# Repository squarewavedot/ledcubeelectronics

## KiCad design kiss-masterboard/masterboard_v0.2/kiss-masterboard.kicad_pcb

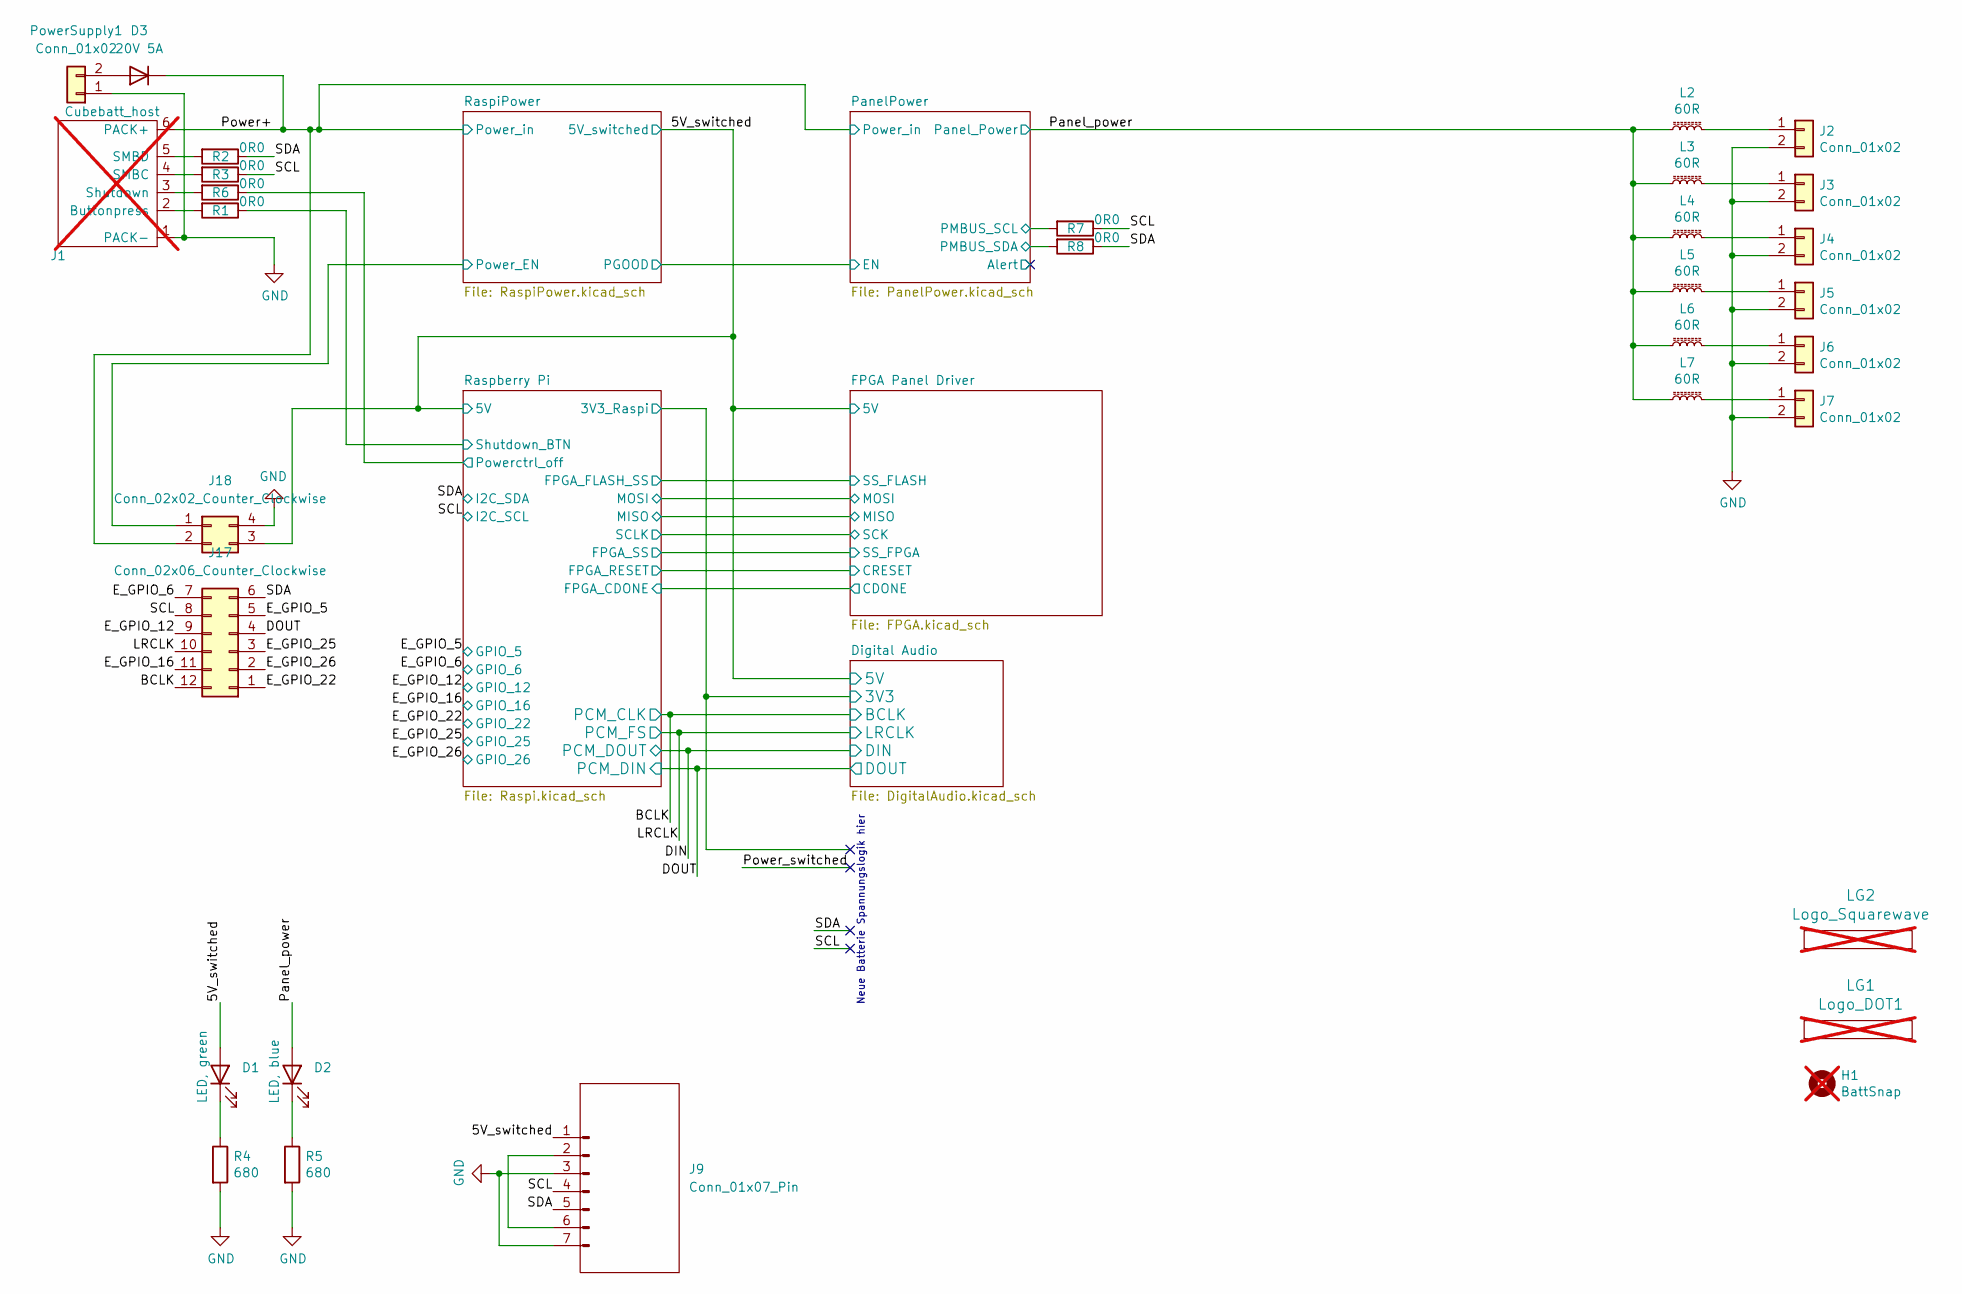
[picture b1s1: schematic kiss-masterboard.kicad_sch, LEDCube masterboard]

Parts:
D1: LED, green; LED_0603_1608Metric; Part No. LG Q971-KN-1; LCSC Part # C2290
D2: LED, blue; LED_0603_1608Metric; Part No. LB Q39G-L2N2-35-1; LCSC Part # C2286
D3: 20V 5A; D_SMA; LCSC Part # C5818966
H1: BattSnap; batt_snap; not fitted
J1: Cubebatt_host; cubebatt_host; not fitted
J2, J3, J4, J5, J6, J7: Conn_01x02; JST_VH_B2P-VH_1x02_P3.96mm_Vertical
J9: Conn_01x07_Pin; PinHeader_1x07_imu
J17: Conn_02x06_Counter_Clockwise; PinSocket_2x06_P2.54mm_Vertical_SMD; LCSC Part # C32713286
J18: Conn_02x02_Counter_Clockwise; PinSocket_2x02_P2.54mm_Vertical_SMD; LCSC Part # C919361
L2, L3, L4, L5, L6, L7: 60R; L_1008_2520Metric; Part No. FBMJ3216HM600-T; Digikey No. 587-1770-1-ND
LG1: Logo_DOT1; Logo_Dot_15mm_Text_Mask; not fitted
LG2: Logo_Squarewave; Logo_Squarewave_Text_15mm_Silks; not fitted
PowerSupply1: Conn_01x02; AMASS_XT30PW-F_1x02_P2.50mm_Horizontal
R1, R2, R3, R6, R7, R8: 0R0; R_0603_1608Metric; Part No. RC0603JR-07680R; LCSC Part # C21189
R4, R5: 680; R_0603_1608Metric; Part No. RC0603JR-07680R; LCSC Part # C23228

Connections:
/5V_switched: D1.2 (A), J9.1, J18.3; also elsewhere on the board
/BCLK: J17.12; also elsewhere on the board
/DOUT: J17.4; also elsewhere on the board
/E_GPIO_5: J17.5; also elsewhere on the board
/E_GPIO_6: J17.7; also elsewhere on the board
/E_GPIO_12: J17.9; also elsewhere on the board
/E_GPIO_16: J17.11; also elsewhere on the board
/E_GPIO_22: J17.1; also elsewhere on the board
/E_GPIO_25: J17.3; also elsewhere on the board
/E_GPIO_26: J17.2; also elsewhere on the board
/LRCLK: J17.10; also elsewhere on the board
/PanelPower/PMBUS_SCL: R7.2; also elsewhere on the board
/PanelPower/PMBUS_SDA: R8.2; also elsewhere on the board
/Panel_power: D2.2 (A), L2.1, L3.1, L4.1, L5.1, L6.1, L7.1; also elsewhere on the board
/Power+: D3.1 (K), J1.6 (PACK+), J18.2; also elsewhere on the board
/Raspberry Pi/Powerctrl_off: R6.1; also elsewhere on the board
/Raspberry Pi/Shutdown_BTN: R1.1; also elsewhere on the board
/RaspiPower/Power_EN: J18.1; also elsewhere on the board
/SCL: J9.4, J17.8, R3.1, R7.1; also elsewhere on the board
/SDA: J9.5, J17.6, R2.1, R8.1; also elsewhere on the board
GND: J1.1 (PACK-), J2.2, J3.2, J4.2, J5.2, J6.2, J7.2, J9.3, J9.7, J18.4, PowerSupply1.1, R4.2, R5.2; also elsewhere on the board
unnamed: D1.1 (K), R4.1
unnamed: D2.1 (K), R5.1
unnamed: D3.2 (A), PowerSupply1.2
unnamed: J1.2 (Buttonpress), R1.2
unnamed: J1.4 (SMBC), R3.2
unnamed: J1.5 (SMBD), R2.2
unnamed: J1.3 (Shutdown), R6.2
unnamed: J2.1, L2.2
unnamed: J3.1, L3.2
unnamed: J4.1, L4.2
unnamed: J5.1, L5.2
unnamed: J6.1, L6.2
unnamed: J7.1, L7.2
unnamed: J9.2, J9.6

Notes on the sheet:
Neue Batterie Spannungslogik hier

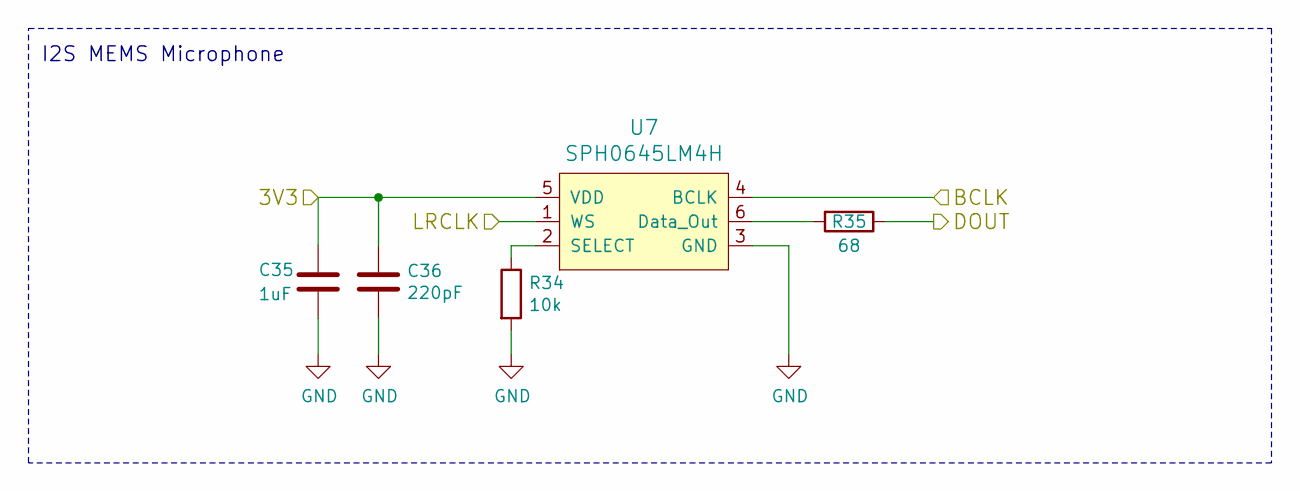
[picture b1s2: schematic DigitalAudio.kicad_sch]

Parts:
C35: 1uF; C_0603_1608Metric; LCSC Part # C15849
C36: 220pF; C_0603_1608Metric; LCSC Part # C1603
R34: 10k; R_0603_1608Metric; LCSC Part # C25804
R35: 68; R_0603_1608Metric; LCSC Part # C27592
U7: SPH0645LM4H

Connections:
/BCLK: U7.4 (BCLK); also elsewhere on the board
/DOUT: R35.1; also elsewhere on the board
/LRCLK: U7.1 (WS); also elsewhere on the board
/Raspberry Pi/3v3: C35.1, C36.1, U7.5 (VDD); also elsewhere on the board
GND: C35.2, C36.2, R34.2, U7.3 (GND); also elsewhere on the board
unnamed: R35.2, U7.6 (Data_Out)
unnamed: R34.1, U7.2 (SELECT)

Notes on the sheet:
I2S MEMS Microphone

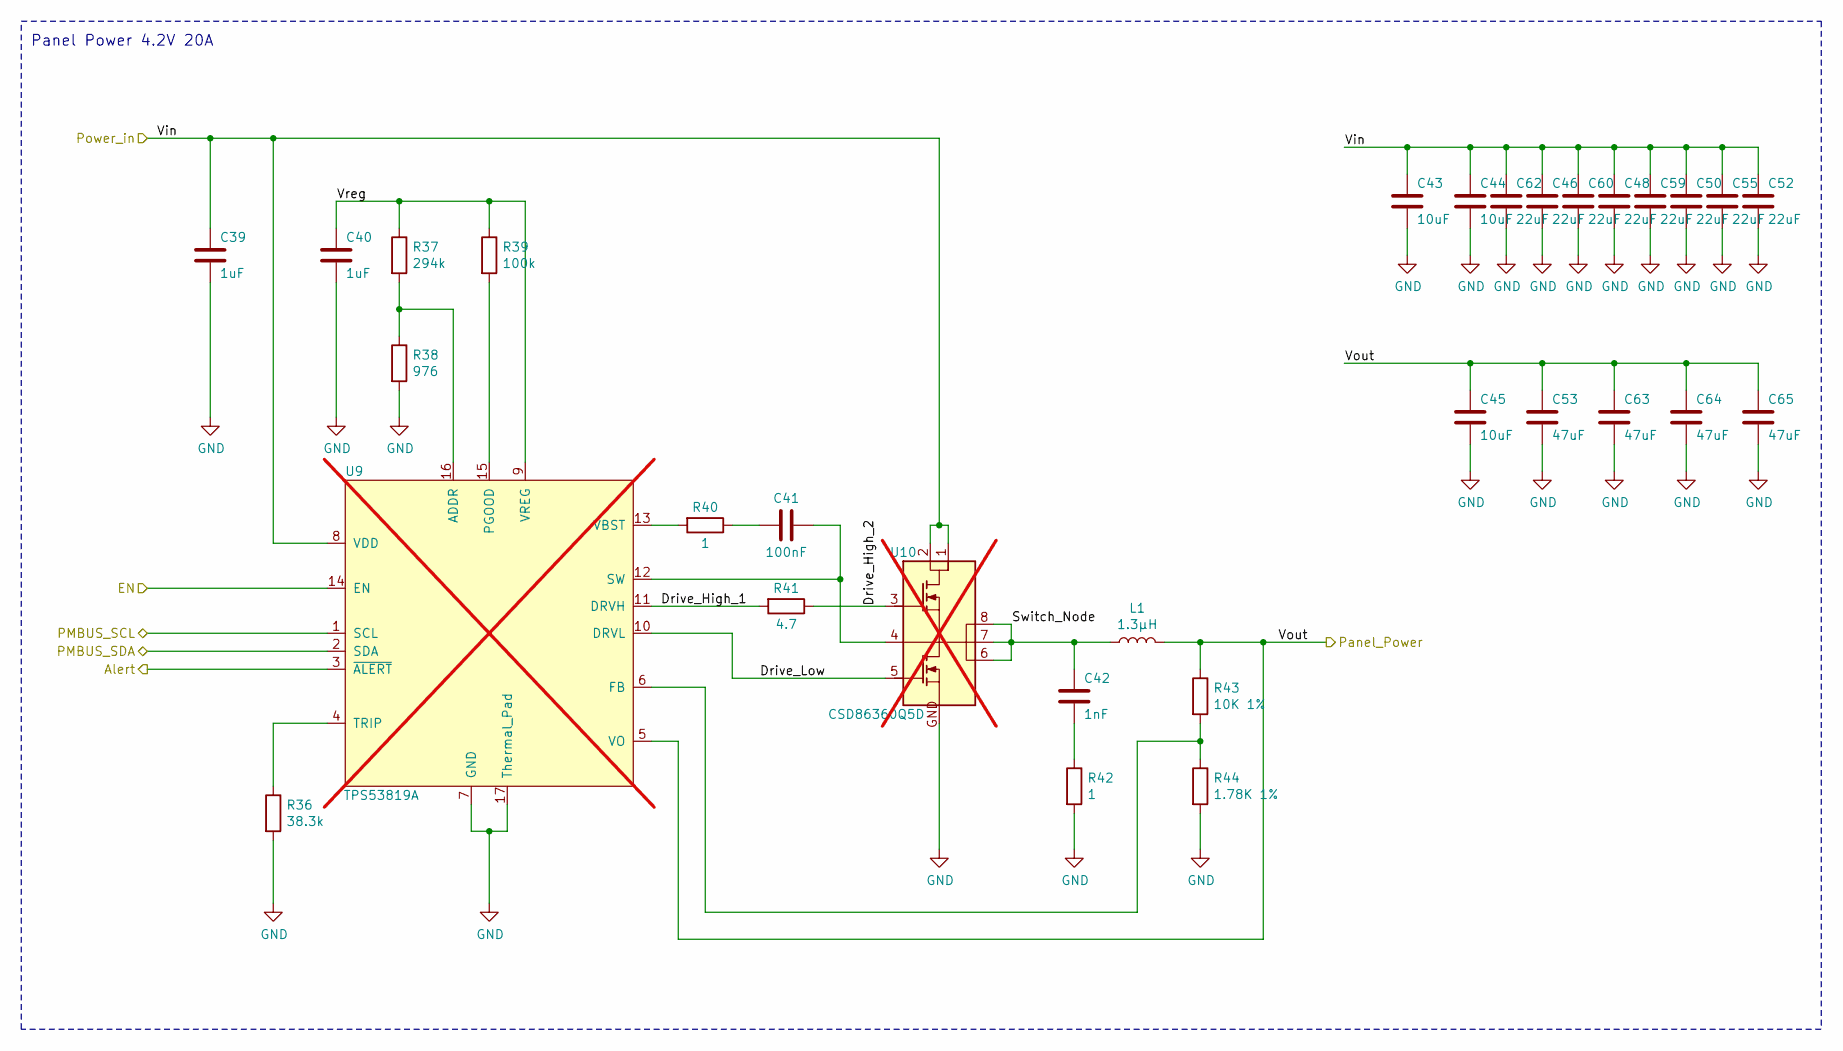
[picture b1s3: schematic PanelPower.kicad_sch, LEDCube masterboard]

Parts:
C39: 1uF; C_0805_2012Metric; Part No. GMK212B7105KG-T; Digikey No. 587-1438-1-ND
C40: 1uF; C_0603_1608Metric; Part No. GMK212B7105KG-T; Digikey No. 587-1438-1-ND
C41: 100nF; C_0805_2012Metric; Part No. CGA4J2X7R2A104K125AA; Digikey No. 445-5827-1-ND
C42: 1nF; C_0603_1608Metric; Part No. C0603C102J5RACTU; Digikey No. 399-1083-1-ND
C43, C44, C45: 10uF; C_1206_3216Metric; Part No. GRM21BR61E106MA73L; Digikey No. 490-10748-1-ND
C46, C48, C50, C52, C55, C59, C60, C62: 22uF; C_1206_3216Metric; Part No. C12891; LCSC Part # C12891
C53, C63, C64, C65: 47uF; C_1206_3216Metric; Part No. C12891; LCSC Part # C96123
L1: 1.3µH; Coilcraft_XAL1580; Part No. XAL1580-132MEB; Digikey No. Mouser
R36: 38.3k; R_0603_1608Metric; Part No. RMCF0603FT38K3; Digikey No. RMCF0603FT38K3CT-ND
R37: 294k; R_0402_1005Metric; Part No. CRCW0402294KFKED; Digikey No. 541-294KLCT-ND
R38: 976; R_0402_1005Metric; Part No. CRCW0402976RFKED; Digikey No. 541-976LCT-ND
R39: 100k; R_0603_1608Metric; Part No. RC0603JR-07100K; LCSC Part # C25803
R40, R42: 1; R_0805_2012Metric; Part No. CRCW08051R00FKEA; Digikey No. 541-1.00CCCT-ND
R41: 4.7; R_0805_2012Metric; Part No. ERJ-6RQF4R7V; Digikey No. P4.7DCT-ND
R43: 10K 1%; R_0603_1608Metric; Part No. RNCP0603FTD10K0; Digikey No. RNCP0603FTD10K0CT-ND
R44: 1.78K 1%; R_0603_1608Metric; Part No. RC0603FR-0717K8L; Digikey No. 311-17.8KHRCT-ND
U9: TPS53819A; VQFN-16-1EP_3x3mm_P0.5mm_EP1.68x1.68mm_ThermalVias; Part No. TPS53819ARGTR; Digikey No. 296-35480-1-ND; not fitted
U10: CSD86360Q5D; Q5D; Part No. CSD86360Q5D; Digikey No. 296-35026-1-ND; not fitted

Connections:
/5V_switched: U9.14 (EN); also elsewhere on the board
/PanelPower/Alert: U9.3 (~ALERT)
/PanelPower/Drive_High_1: R41.2, U9.11 (DRVH)
/PanelPower/Drive_High_2: R41.1, U10.3 (TG)
/PanelPower/Drive_Low: U9.10 (DRVL), U10.5 (BG)
/PanelPower/PMBUS_SCL: U9.1 (SCL); also elsewhere on the board
/PanelPower/PMBUS_SDA: U9.2 (SDA); also elsewhere on the board
/PanelPower/Switch_Node: C42.1, L1.1, U10.6 (VSW), U10.7 (VSW), U10.8 (VSW)
/PanelPower/Vreg: C40.1, R37.1, R39.1, U9.9 (VREG)
/Panel_power: C45.1, C53.1, C63.1, C64.1, C65.1, L1.2, R43.1, U9.5 (VO); also elsewhere on the board
/Power+: C39.1, C43.1, C44.1, C46.1, C48.1, C50.1, C52.1, C55.1, C59.1, C60.1, C62.1, U9.8 (VDD), U10.1 (VIN), U10.2 (VIN); also elsewhere on the board
GND: C39.2, C40.2, C43.2, C44.2, C45.2, C46.2, C48.2, C50.2, C52.2, C53.2, C55.2, C59.2, C60.2, C62.2, C63.2, C64.2, C65.2, R36.2, R38.2, R42.2, R44.2, U9.7 (GND), U9.17 (Thermal_Pad), U10.GND; also elsewhere on the board
unnamed: C41.2, R40.1
unnamed: C42.2, R42.1
unnamed: R37.2, R38.1, U9.16 (ADDR)
unnamed: R43.2, R44.1, U9.6 (FB)
unnamed: R39.2, U9.15 (PGOOD)
unnamed: R36.1, U9.4 (TRIP)
unnamed: R40.2, U9.13 (VBST)
unnamed: C41.1, U9.12 (SW), U10.4 (TGR)

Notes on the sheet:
Panel Power 4.2V 20A

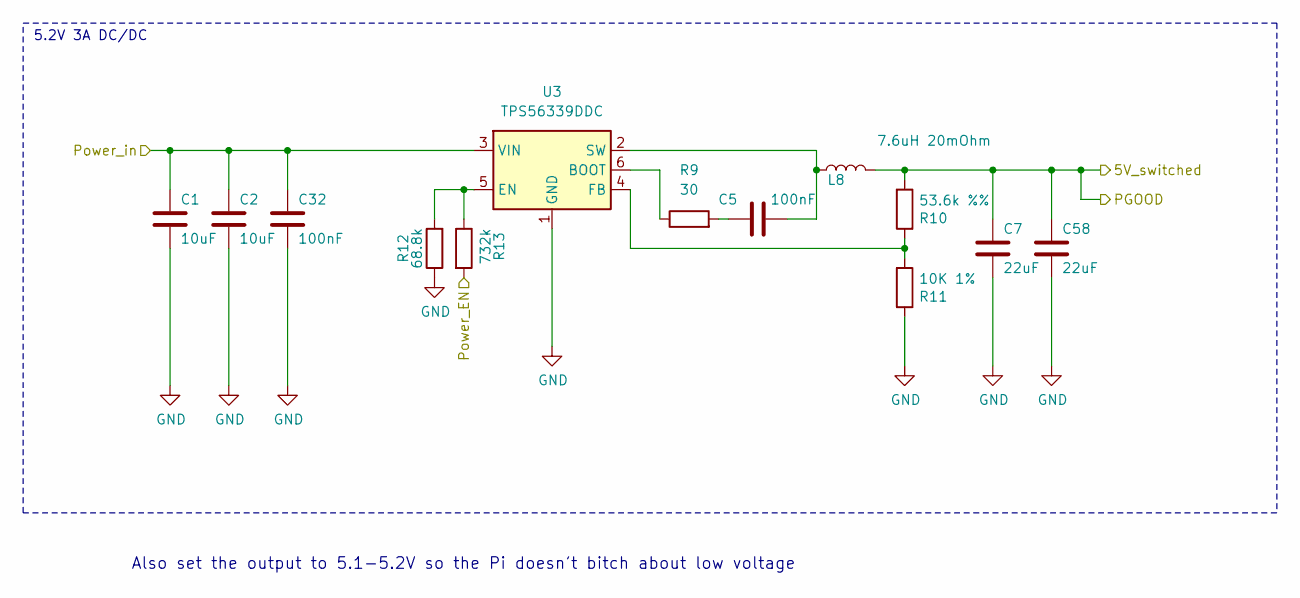
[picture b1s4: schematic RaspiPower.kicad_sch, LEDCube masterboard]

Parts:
C1, C2: 10uF; C_0805_2012Metric; Part No. GRM21BR61E106MA73L; Digikey No. 490-10748-1-ND
C5: 100nF; C_0603_1608Metric; Part No. GRM188R71H103KA01D; LCSC Part # C14663
C7, C58: 22uF; C_1206_3216Metric; Part No. LMK325BJ107MM-T; Digikey No. 587-1965-1-ND
C32: 100nF; C_0603_1608Metric; Part No. GMK212B7105KG-T; Digikey No. 587-1438-1-ND
L8: 7.6uH 20mOhm; L_12x12mm_H4.5mm; LCSC Part # C3040411
R9: 30; R_0603_1608Metric; LCSC Part # C217958
R10: 53.6k %%; R_0603_1608Metric; Part No. RC0603JR-0768K; LCSC Part # C2930115
R11: 10K 1%; R_0603_1608Metric; Part No. RC0603JR-0768K; LCSC Part # C25804
R12: 68.8k; R_0603_1608Metric_Pad0.98x0.95mm_HandSolder; LCSC Part # C23231
R13: 732k; R_0603_1608Metric_Pad0.98x0.95mm_HandSolder; LCSC Part # C5159703
U3: TPS56339DDC; SOT-23-6; LCSC Part # C2071106

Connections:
/5V_switched: C7.1, C58.1, L8.2, R10.2; also elsewhere on the board
/Power+: C1.1, C2.1, C32.1, U3.3 (VIN); also elsewhere on the board
/RaspiPower/Power_EN: R13.2; also elsewhere on the board
GND: C1.2, C2.2, C7.2, C32.2, C58.2, R11.1, R12.1, U3.1 (GND); also elsewhere on the board
unnamed: C5.1, R9.2
unnamed: R9.1, U3.6 (BOOT)
unnamed: R12.2, R13.1, U3.5 (EN)
unnamed: R10.1, R11.2, U3.4 (FB)
unnamed: C5.2, L8.1, U3.2 (SW)

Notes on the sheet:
Also set the output to 5.1-5.2V so the Pi doesn't bitch about low voltage
5.2V 3A DC/DC

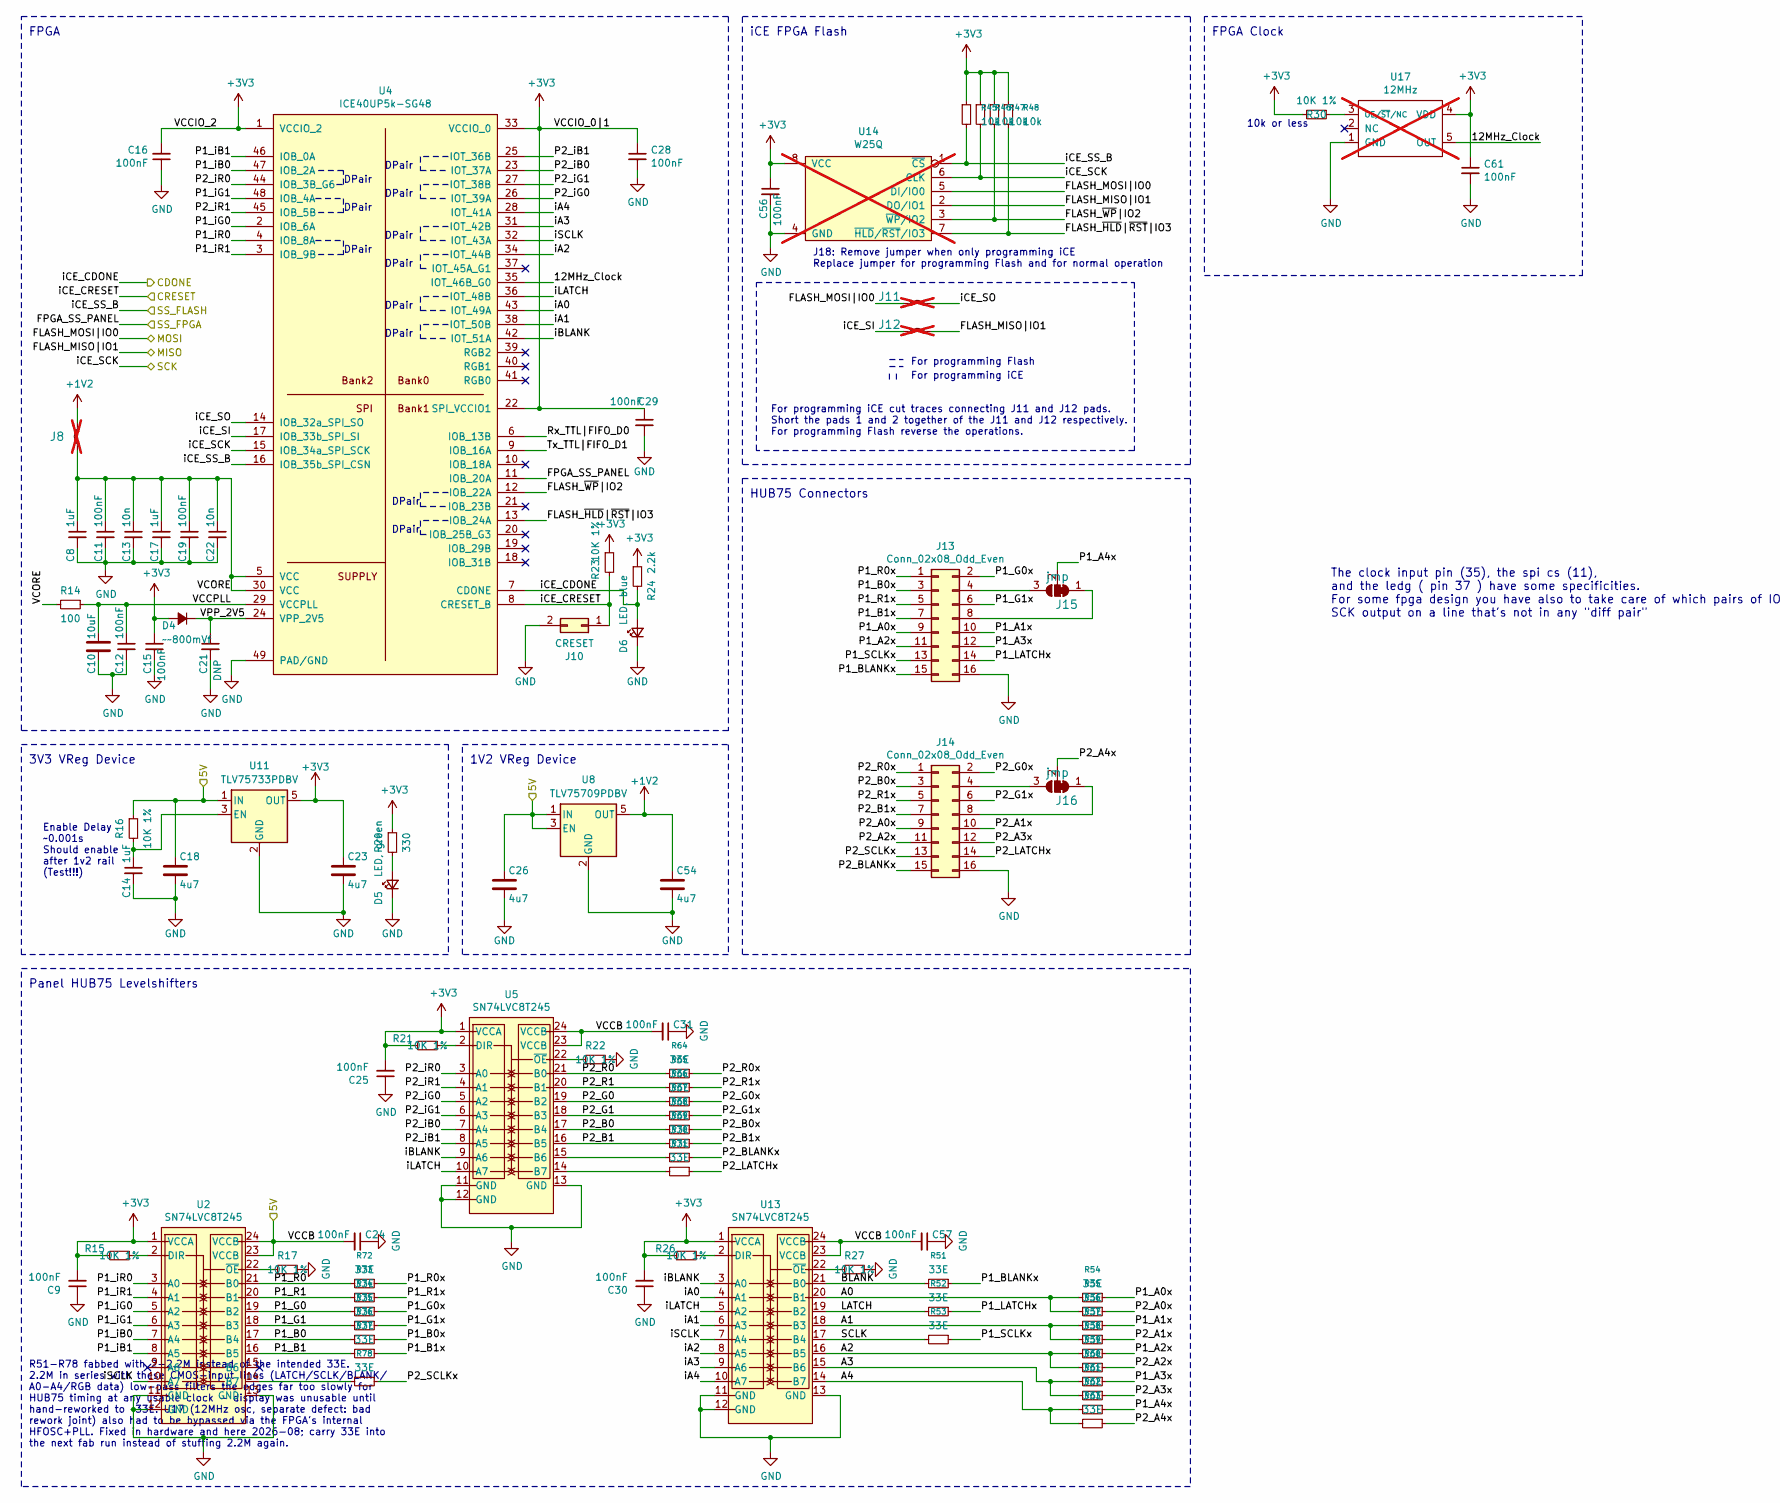
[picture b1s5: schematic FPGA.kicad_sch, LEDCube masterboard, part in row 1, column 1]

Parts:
C8, C14, C17: 1uF; C_0402_1005Metric; LCSC Part # C52923
C9, C11, C12, C15, C16, C19, C24, C25, C28, C29, C30, C31, C57, C61: 100nF; C_0402_1005Metric; LCSC Part # C1525
C10: 10uF; C_0603_1608Metric; LCSC Part # C19702
C13, C22: 10n; C_0402_1005Metric; LCSC Part # C15195
C18, C23, C26, C54: 4u7; C_0603_1608Metric; LCSC Part # C19666
C21: DNP; C_0402_1005Metric
C56: 100nF; C_0603_1608Metric; LCSC Part # C14663
D4: ~~800mVf; D_SOD-523; LCSC Part # C7502714
D5: LED, green; LED_0603_1608Metric; LCSC Part # C2290
D6: LED, blue; LED_0603_1608Metric; LCSC Part # C2286
J8: Jumper; SolderJumper-2_P1.3mm_Bridged_Pad1.0x1.5mm; not fitted
J10: CRESET; PinHeader_2x01_P2.54mm_Vertical
J11, J12: Jumper; SolderJumper-2_P1.3mm_Bridged2Bar_Pad1.0x1.5mm; not fitted
J13, J14: Conn_02x08_Odd_Even; PinHeader_2x08_P2.54mm_Vertical_SMD_IDC; LCSC Part # C2843216
J15, J16: jmp; SolderJumper-3_P1.3mm_Bridged12_Pad1.0x1.5mm_NumberLabels
R14: 100; R_0402_1005Metric; LCSC Part # C25076
R15, R16, R17, R21, R22, R23, R26, R27, R30: 10K 1%; R_0402_1005Metric; LCSC Part # C25744
R20: 330; R_0402_1005Metric; LCSC Part # C25104
R24: 2.2k; R_0402_1005Metric; LCSC Part # C25879
R45, R46, R47, R48: 10k; R_0603_1608Metric; LCSC Part # C25804
R51, R52, R53, R54, R55, R56, R57, R58, R59, R60, R61, R62, R63, R64, R65, R66, R67, R68, R69, R70, R71, R72, R73, R74, R75, R76, R77, R78: 33E; R_0402; LCSC Part # C138015
U2, U5, U13: SN74LVC8T245; TSSOP-24_4.4x7.8mm_P0.65mm; LCSC Part # C27643
U4: ICE40UP5k-SG48; QFN-48-1EP_7x7mm_Pitch0.5mm; LCSC Part # C2678152
U8: TLV75709PDBV; SOT-23-5; LCSC Part # C58464
U11: TLV75733PDBV; SOT-23-5; LCSC Part # C485517
U14: W25Q; SOIC-8_5.3x5.3mm_Pitch1.27mm; not fitted
U17: 12MHz; SOT-23-5; not fitted

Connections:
+1V2: C54.1, J8.2 (B), U8.5 (OUT)
+3V3: C9.2, C15.1, C16.2, C23.1, C25.2, C28.1, C29.1, C30.2, C56.1, C61.1, D4.A, R15.2, R20.1, R21.2, R23.1, R24.1, R26.1, R30.2, R45.1, R46.1, R47.1, R48.1, U2.1 (VCCA), U4.1 (VCCIO_2), U4.22 (SPI_VCCIO1), U4.33 (VCCIO_0), U5.1 (VCCA), U11.5 (OUT), U13.1 (VCCA), U14.8 (VCC), U17.4 (VDD)
/5V_switched: C18.1, C24.2, C26.1, C31.2, C57.2, R16.1, U2.23 (VCCB), U2.24 (VCCB), U5.23 (VCCB), U5.24 (VCCB), U8.1 (IN), U8.3 (EN), U11.1 (IN), U13.23 (VCCB), U13.24 (VCCB); also elsewhere on the board
/FPGA Panel Driver/12MHz_Clock: U4.35 (IOT_46B_G0), U17.5 (OUT)
/FPGA Panel Driver/A0: R54.2, R55.2, U13.20 (B1)
/FPGA Panel Driver/A1: R56.2, R57.2, U13.18 (B3)
/FPGA Panel Driver/A2: R58.2, R59.2, U13.16 (B5)
/FPGA Panel Driver/A3: R60.2, R61.2, U13.15 (B6)
/FPGA Panel Driver/A4: R62.2, R63.2, U13.14 (B7)
/FPGA Panel Driver/BLANK: R51.2, U13.21 (B0)
/FPGA Panel Driver/FLASH_MISO|IO1: J12.2 (B), U14.2 (DO/IO1); also elsewhere on the board
/FPGA Panel Driver/FLASH_MOSI|IO0: J11.1 (A), U14.5 (DI/IO0); also elsewhere on the board
/FPGA Panel Driver/FLASH_~HLD|~RST|IO3: R48.2, U4.13 (IOB_24A), U14.7 (~HLD/~RST/IO3)
/FPGA Panel Driver/FLASH_~WP|IO2: R47.2, U4.12 (IOB_22A), U14.3 (~WP/IO2)
/FPGA Panel Driver/FPGA_SS_PANEL: U4.11 (IOB_20A); also elsewhere on the board
/FPGA Panel Driver/LATCH: R52.2, U13.19 (B2)
/FPGA Panel Driver/P1_A0x: J13.9, R54.1
/FPGA Panel Driver/P1_A1x: J13.10, R56.1
/FPGA Panel Driver/P1_A2x: J13.11, R58.1
/FPGA Panel Driver/P1_A3x: J13.12, R60.1
/FPGA Panel Driver/P1_A4x: J15.2 (C), R62.1
/FPGA Panel Driver/P1_B0: R76.2, U2.17 (B4)
/FPGA Panel Driver/P1_B0x: J13.3, R76.1
/FPGA Panel Driver/P1_B1: R77.2, U2.16 (B5)
/FPGA Panel Driver/P1_B1x: J13.7, R77.1
/FPGA Panel Driver/P1_BLANKx: J13.15, R51.1
/FPGA Panel Driver/P1_G0: R74.2, U2.19 (B2)
/FPGA Panel Driver/P1_G0x: J13.2, R74.1
/FPGA Panel Driver/P1_G1: R75.2, U2.18 (B3)
/FPGA Panel Driver/P1_G1x: J13.6, R75.1
/FPGA Panel Driver/P1_LATCHx: J13.14, R52.1
/FPGA Panel Driver/P1_R0: R72.2, U2.21 (B0)
/FPGA Panel Driver/P1_R0x: J13.1, R72.1
/FPGA Panel Driver/P1_R1: R73.2, U2.20 (B1)
/FPGA Panel Driver/P1_R1x: J13.5, R73.1
/FPGA Panel Driver/P1_SCLKx: J13.13, R53.1
/FPGA Panel Driver/P1_iB0: U2.7 (A4), U4.47 (IOB_2A)
/FPGA Panel Driver/P1_iB1: U2.8 (A5), U4.46 (IOB_0A)
/FPGA Panel Driver/P1_iG0: U2.5 (A2), U4.2 (IOB_6A)
/FPGA Panel Driver/P1_iG1: U2.6 (A3), U4.48 (IOB_4A)
/FPGA Panel Driver/P1_iR0: U2.3 (A0), U4.4 (IOB_8A)
/FPGA Panel Driver/P1_iR1: U2.4 (A1), U4.3 (IOB_9B)
/FPGA Panel Driver/P2_A0x: J14.9, R55.1
/FPGA Panel Driver/P2_A1x: J14.10, R57.1
/FPGA Panel Driver/P2_A2x: J14.11, R59.1
/FPGA Panel Driver/P2_A3x: J14.12, R61.1
/FPGA Panel Driver/P2_A4x: J16.2 (C), R63.1
/FPGA Panel Driver/P2_B0: R68.2, U5.17 (B4)
/FPGA Panel Driver/P2_B0x: J14.3, R68.1
/FPGA Panel Driver/P2_B1: R69.2, U5.16 (B5)
/FPGA Panel Driver/P2_B1x: J14.7, R69.1
/FPGA Panel Driver/P2_BLANKx: J14.15, R70.1
/FPGA Panel Driver/P2_G0: R66.2, U5.19 (B2)
/FPGA Panel Driver/P2_G0x: J14.2, R66.1
/FPGA Panel Driver/P2_G1: R67.2, U5.18 (B3)
/FPGA Panel Driver/P2_G1x: J14.6, R67.1
/FPGA Panel Driver/P2_LATCHx: J14.14, R71.1
/FPGA Panel Driver/P2_R0: R64.2, U5.21 (B0)
/FPGA Panel Driver/P2_R0x: J14.1, R64.1
/FPGA Panel Driver/P2_R1: R65.2, U5.20 (B1)
/FPGA Panel Driver/P2_R1x: J14.5, R65.1
/FPGA Panel Driver/P2_SCLKx: J14.13, R78.1
/FPGA Panel Driver/P2_iB0: U4.23 (IOT_37A), U5.7 (A4)
/FPGA Panel Driver/P2_iB1: U4.25 (IOT_36B), U5.8 (A5)
/FPGA Panel Driver/P2_iG0: U4.26 (IOT_39A), U5.5 (A2)
/FPGA Panel Driver/P2_iG1: U4.27 (IOT_38B), U5.6 (A3)
/FPGA Panel Driver/P2_iR0: U4.44 (IOB_3B_G6), U5.3 (A0)
/FPGA Panel Driver/P2_iR1: U4.45 (IOB_5B), U5.4 (A1)
/FPGA Panel Driver/Rx_TTL|FIFO_D0: U4.6 (IOB_13B)
/FPGA Panel Driver/SCLK: R53.2, U13.17 (B4)
/FPGA Panel Driver/Tx_TTL|FIFO_D1: U4.9 (IOB_16A)
/FPGA Panel Driver/VCCPLL: C10.1, C12.1, R14.1, U4.29 (VCCPLL)
/FPGA Panel Driver/VCORE: C8.1, C11.1, C13.1, C17.1, C19.1, C22.1, J8.1 (A), R14.2, U4.5 (VCC), U4.30 (VCC)
/FPGA Panel Driver/VPP_2V5: C21.1, D4.C, U4.24 (VPP_2V5)
/FPGA Panel Driver/iA0: U4.43 (IOT_49A), U13.4 (A1)
/FPGA Panel Driver/iA1: U4.38 (IOT_50B), U13.6 (A3)
/FPGA Panel Driver/iA2: U4.34 (IOT_44B), U13.8 (A5)
/FPGA Panel Driver/iA3: U4.31 (IOT_42B), U13.9 (A6)
/FPGA Panel Driver/iA4: U4.28 (IOT_41A), U13.10 (A7)
/FPGA Panel Driver/iBLANK: U4.42 (IOT_51A), U5.9 (A6), U13.3 (A0)
/FPGA Panel Driver/iCE_CDONE: D6.2 (A), R24.2, U4.7 (CDONE); also elsewhere on the board
/FPGA Panel Driver/iCE_CRESET: J10.1, R23.2, U4.8 (CRESET_B); also elsewhere on the board
/FPGA Panel Driver/iCE_SCK: R46.2, U4.15 (IOB_34a_SPI_SCK), U14.6 (CLK); also elsewhere on the board
/FPGA Panel Driver/iCE_SI: J12.1 (A), U4.17 (IOB_33b_SPI_SI)
/FPGA Panel Driver/iCE_SO: J11.2 (B), U4.14 (IOB_32a_SPI_SO)
/FPGA Panel Driver/iCE_SS_B: R45.2, U4.16 (IOB_35b_SPI_CSN), U14.1 (~CS); also elsewhere on the board
/FPGA Panel Driver/iLATCH: U4.36 (IOT_48B), U5.10 (A7), U13.5 (A2)
/FPGA Panel Driver/iSCLK: U2.10 (A7), U4.32 (IOT_43A), U13.7 (A4)
GND: C8.2, C9.1, C10.2, C11.2, C12.2, C13.2, C14.2, C15.2, C16.1, C17.2, C18.2, C19.2, C21.2, C22.2, C23.2, C24.1, C25.1, C26.2, C28.2, C29.2, C30.1, C31.1, C54.2, C56.2, C57.1, C61.2, D5.1 (K), D6.1 (K), J10.2, J13.16, J14.16, R17.2, R22.2, R27.2, U2.11 (GND), U2.12 (GND), U2.13 (GND), U4.49 (PAD/GND), U5.11 (GND), U5.12 (GND), U5.13 (GND), U8.2 (GND), U11.2 (GND), U13.11 (GND), U13.12 (GND), U13.13 (GND), U14.4 (GND), U17.1 (GND); also elsewhere on the board
unnamed: D5.2 (A), R20.2
unnamed: J13.4, J15.3 (B)
unnamed: J13.8, J15.1 (A)
unnamed: J14.4, J16.3 (B)
unnamed: J14.8, J16.1 (A)
unnamed: R78.2, U2.14 (B7)
unnamed: R15.1, U2.2 (DIR)
unnamed: R17.1, U2.22 (~OE)
unnamed: R70.2, U5.15 (B6)
unnamed: R71.2, U5.14 (B7)
unnamed: R21.1, U5.2 (DIR)
unnamed: R22.1, U5.22 (~OE)
unnamed: C14.1, R16.2, U11.3 (EN)
unnamed: R26.2, U13.2 (DIR)
unnamed: R27.1, U13.22 (~OE)
unnamed: R30.1, U17.3 (OE/~ST/NC)

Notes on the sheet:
DPair
Panel HUB75 Levelshifters
R51-R78 fabbed with 2-2.2M instead of the intended 33E. 2.2M in series with these CMOS-input lines (LATCH/SCLK/BLANK/ A0-A4/RGB data) low-pass filters the edges far too slowly for HUB75 timing at any usable clock - display was unusable until hand-reworked to ~33E. U17 (12MHz osc, separate defect: b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
FPGA
Enable Delay ~0.001s Should enable after 1v2 rail (Test!!!)
For programming iCE cut traces connecting J11 and J12 pads. Short the pads 1 and 2 together of the J11 and J12 respectively. For programming Flash reverse the operations.
1V2 VReg Device
For programming Flash
J18: Remove jumper when only programming iCE Replace jumper for programming Flash and for normal operation
DPair
The clock input pin (35), the spi cs (11), and the ledg ( pin 37 ) have some specificities. For some fpga design you have also to take care of which pairs of IO end up on a given IO site because of shared control lines to the IOB but for the hub75 driver I specifically made sure that all IOs use th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
iCE FPGA Flash
3V3 VReg Device
10k or less
HUB75 Connectors
For programming iCE
FPGA Clock

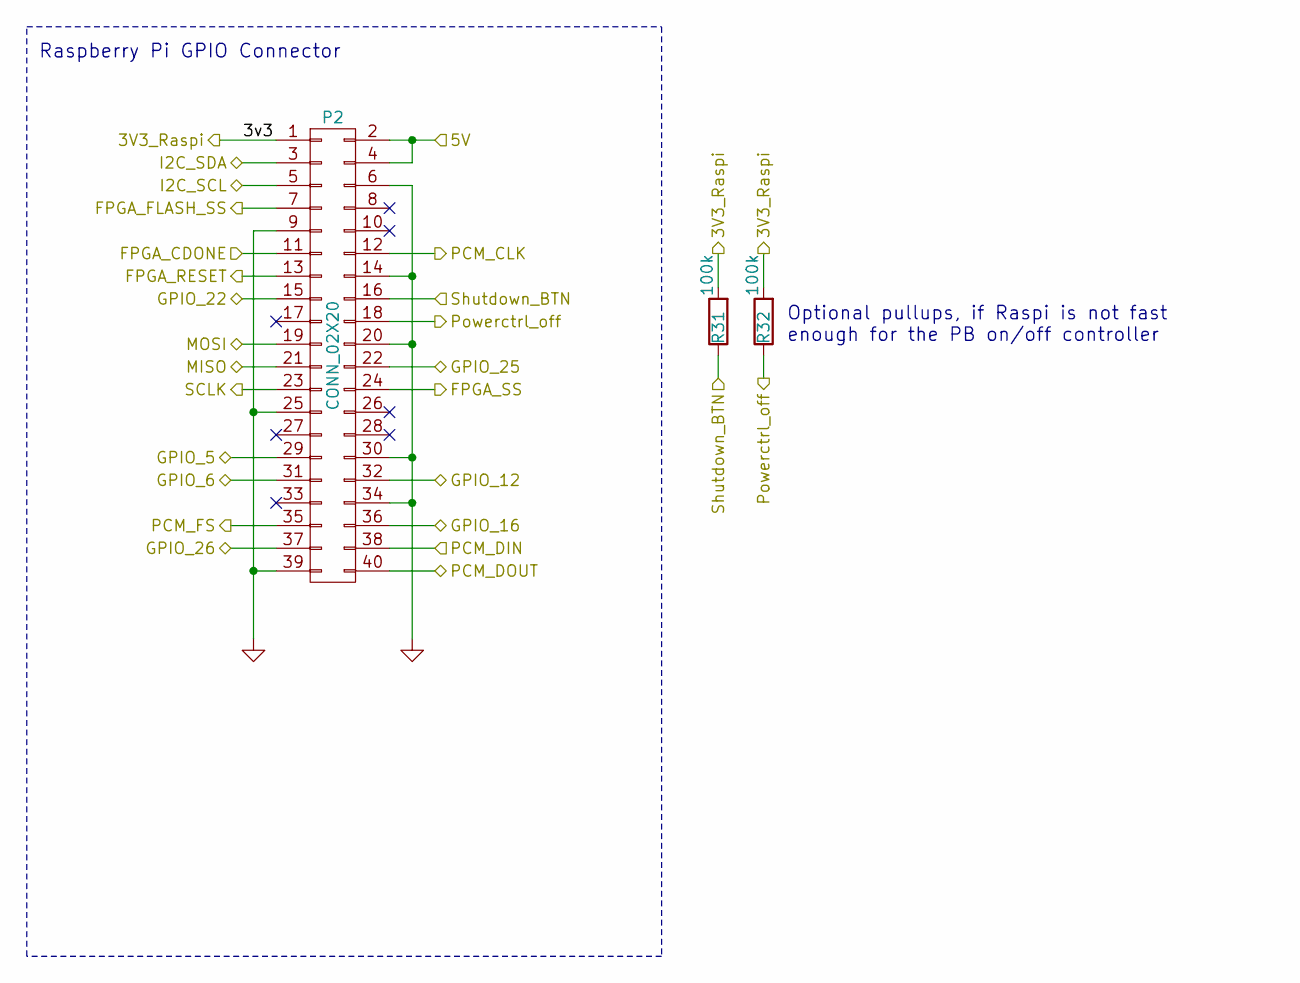
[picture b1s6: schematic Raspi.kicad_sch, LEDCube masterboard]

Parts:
P2: CONN_02X20; raspberrypi_connector_mounting; LCSC Part # C22436166
R31, R32: 100k; R_0603_1608Metric; Part No. RC0603JR-07680R; LCSC Part # C25803

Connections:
/5V_switched: P2.2, P2.4; also elsewhere on the board
/BCLK: P2.12; also elsewhere on the board
/DIN: P2.40
/DOUT: P2.38; also elsewhere on the board
/E_GPIO_5: P2.29; also elsewhere on the board
/E_GPIO_6: P2.31; also elsewhere on the board
/E_GPIO_12: P2.32; also elsewhere on the board
/E_GPIO_16: P2.36; also elsewhere on the board
/E_GPIO_22: P2.15; also elsewhere on the board
/E_GPIO_25: P2.22; also elsewhere on the board
/E_GPIO_26: P2.37; also elsewhere on the board
/FPGA Panel Driver/FLASH_MISO|IO1: P2.21; also elsewhere on the board
/FPGA Panel Driver/FLASH_MOSI|IO0: P2.19; also elsewhere on the board
/FPGA Panel Driver/FPGA_SS_PANEL: P2.24; also elsewhere on the board
/FPGA Panel Driver/iCE_CDONE: P2.11; also elsewhere on the board
/FPGA Panel Driver/iCE_CRESET: P2.13; also elsewhere on the board
/FPGA Panel Driver/iCE_SCK: P2.23; also elsewhere on the board
/FPGA Panel Driver/iCE_SS_B: P2.7; also elsewhere on the board
/LRCLK: P2.35; also elsewhere on the board
/Raspberry Pi/3v3: P2.1, R31.2, R32.2; also elsewhere on the board
/Raspberry Pi/Powerctrl_off: P2.18, R32.1; also elsewhere on the board
/Raspberry Pi/Shutdown_BTN: P2.16, R31.1; also elsewhere on the board
/SCL: P2.5; also elsewhere on the board
/SDA: P2.3; also elsewhere on the board
GND: P2.6, P2.9, P2.14, P2.20, P2.25, P2.30, P2.34, P2.39; also elsewhere on the board

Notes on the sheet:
Raspberry Pi GPIO Connector
Optional pullups, if Raspi is not fast enough for the PB on/off controller

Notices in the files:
kiss-masterboard/masterboard_v0.2/FPGA.kicad_sch:
License: CC-BY-SA V4.0
